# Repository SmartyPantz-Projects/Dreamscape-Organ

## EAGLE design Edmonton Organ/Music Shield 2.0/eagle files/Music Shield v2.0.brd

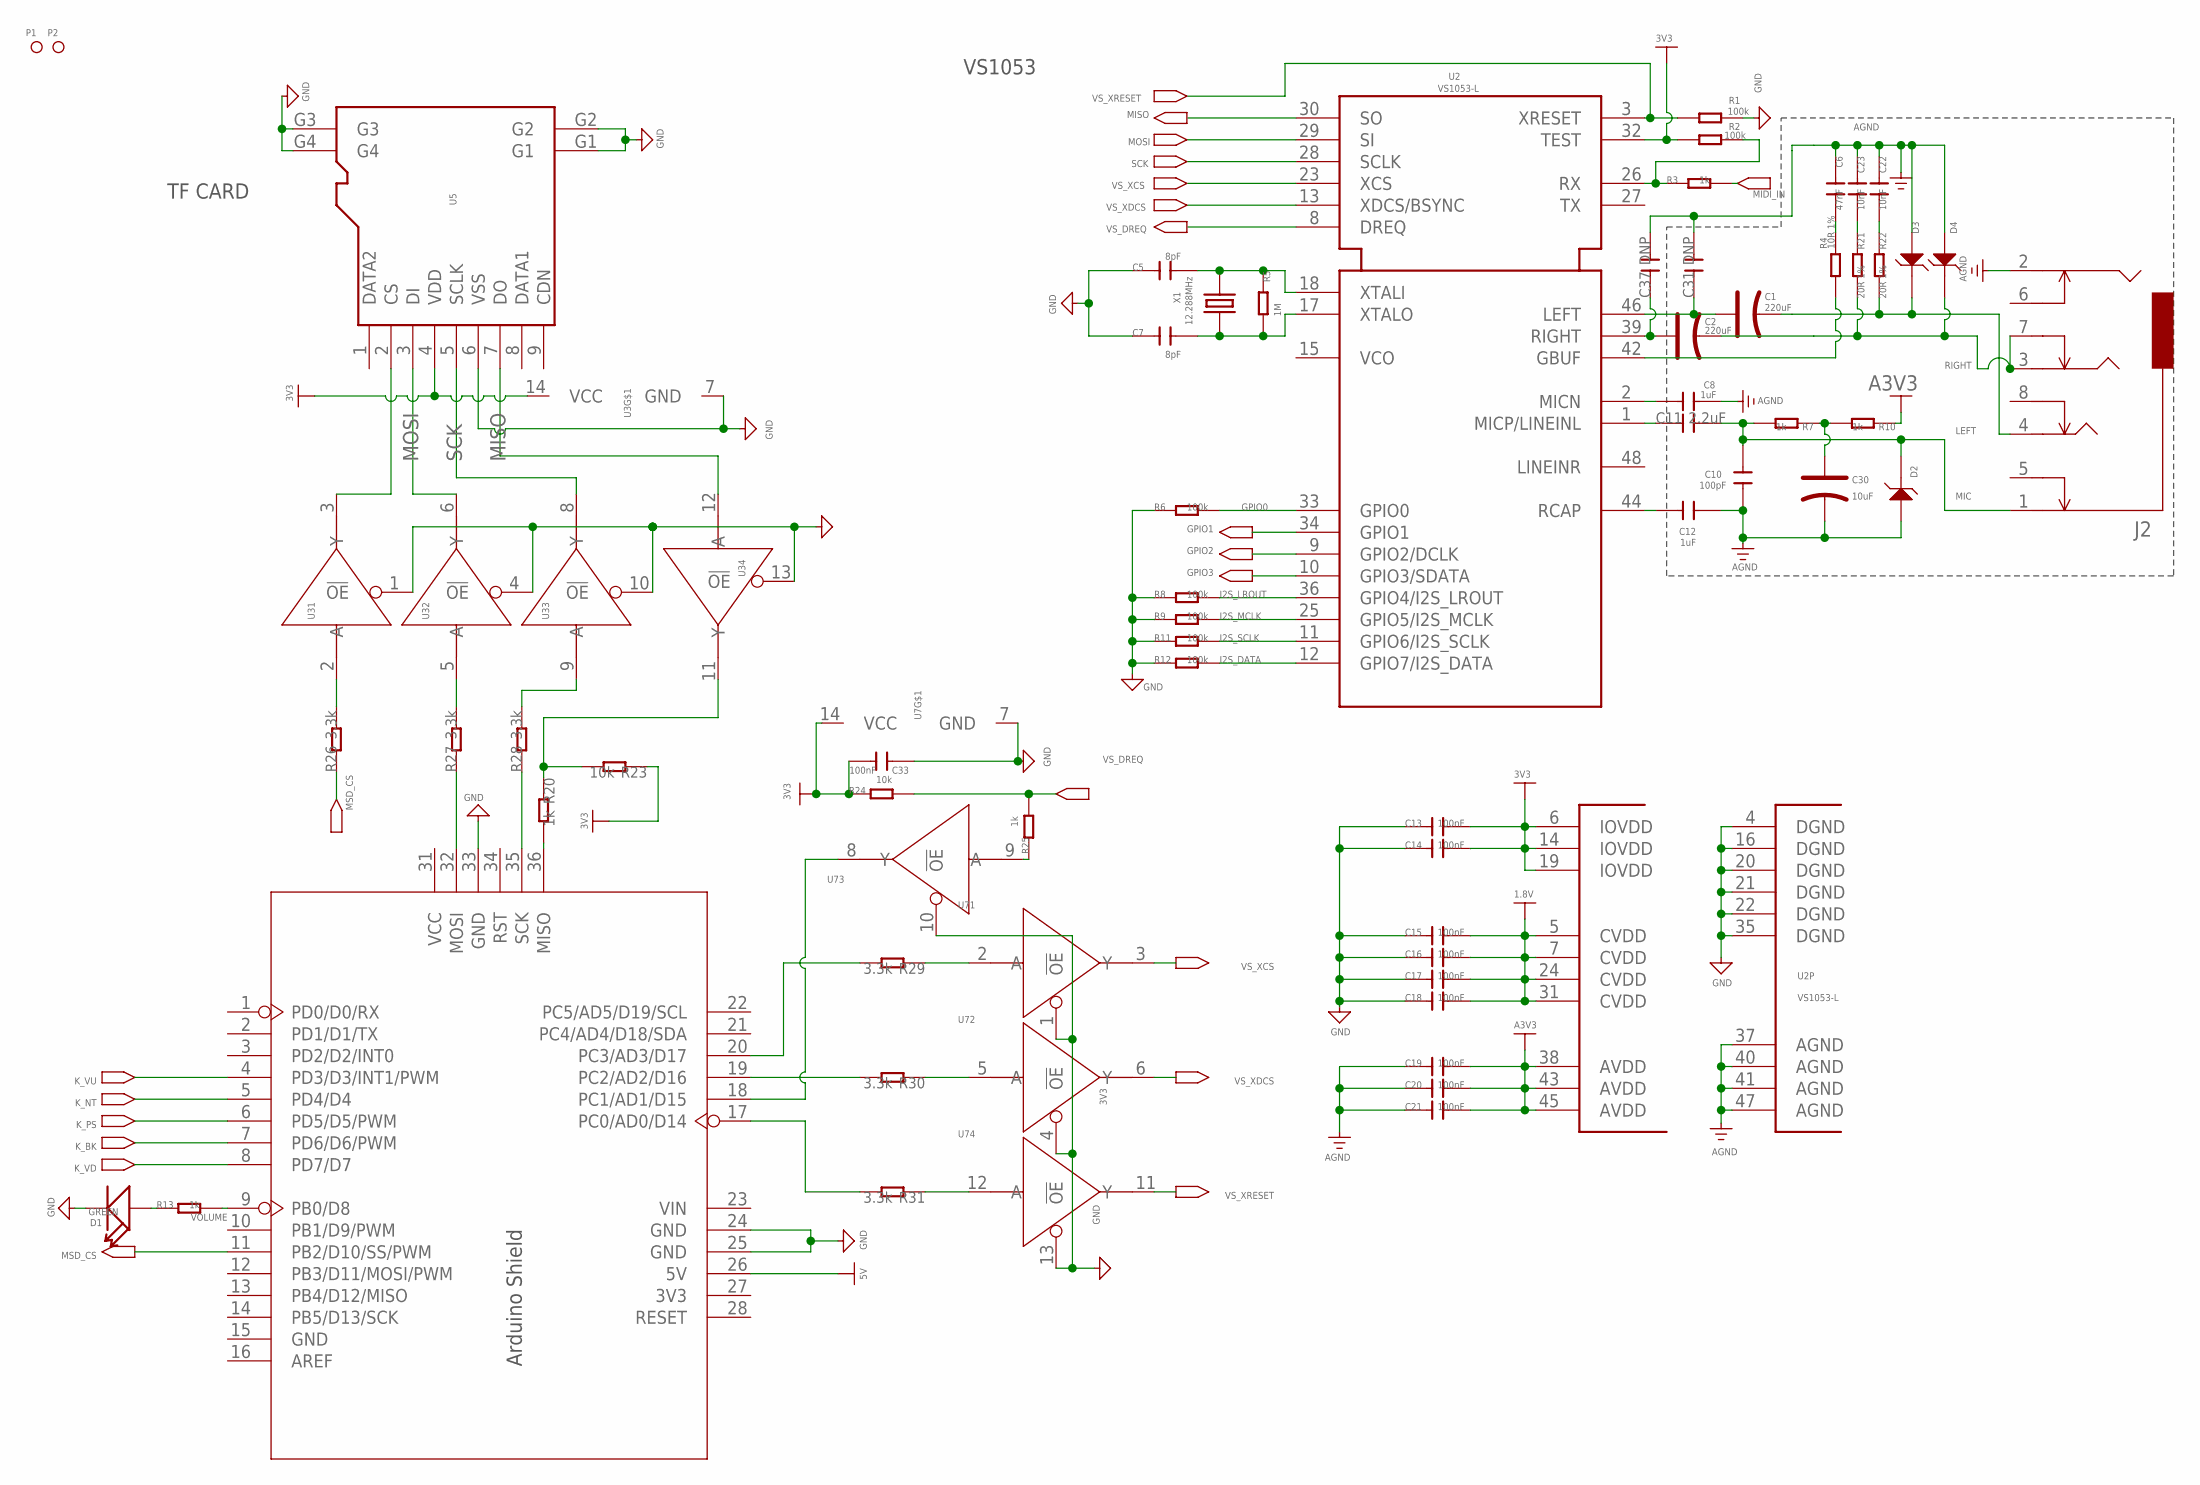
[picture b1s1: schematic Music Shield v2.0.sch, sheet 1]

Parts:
C1, C2: 220uF; AVX-B
C5, C7: 8pF; C0603
C6: 47nF; C0603
C8, C12: 1uF; C0603
C10: 100pF; C0603
C11: 2.2uF; C0805
C13, C14, C15, C16, C17, C18, C19, C20, C21, C33: 100nF; C0603
C22, C23: 10nF; C0603
C30: 10uF; AVX-A
C31, C37: DNP; C0603
D1: GREEN; LED-0603
D2, D3, D4: CESD5V0D1; SOD123-2.7X1.6
J2: AUDIO-8P'PJ-3536-L6S'; 8P-3.5-SMD
P1, P2: PAD-MARK; ROUND-MARK-1.0
R1, R2, R6, R8, R9, R11, R12: 100k; R0603
R3, R7, R10, R13, R20, R25: 1k; R0603
R4: 10R 1%; R0603
R5: 1M; R0603
R21, R22: 20R 1%; R0603
R23, R24: 10k; R0603
R26, R27, R28, R29, R30, R31: 3.3k; R0603
U2: VS1053-L; LQFP48
U3, U7: 74VHC125PW; TSSOP14
U5: HOLDER-MICROSD-9P; 9P-SMD-W/-RING
U9: ARDUINO
X1: 12.288MHz; 2P-SMD-5X3.2

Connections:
1.8V: C15.2, C16.2, C17.2, C18.2, U2.5 (CVDD), U2.7 (CVDD), U2.24 (CVDD), U2.31 (CVDD); also elsewhere on the board
3V3: C13.2, C14.2, C33.2, R2.1, R23.1, R24.1, U2.6 (IOVDD), U2.14 (IOVDD), U2.19 (IOVDD), U2.32 (TEST), U3.14 (VCC), U5.4 (VDD), U7.14 (VCC); also elsewhere on the board
5V: U9.26 (5V); also elsewhere on the board
A3V3: C19.2, C20.2, C21.2, R10.1, U2.38 (AVDD), U2.43 (AVDD), U2.45 (AVDD); also elsewhere on the board
AGND: C6.1, C8.2, C10.2, C12.1, C19.1, C20.1, C21.1, C22.1, C23.1, C30.-, C31.2, C37.2, D2.1, D3.1, D4.1, J2.2, U2.37 (AGND), U2.40 (AGND), U2.41 (AGND), U2.47 (AGND); also elsewhere on the board
GND: C5.1, C7.1, C13.1, C14.1, C15.1, C16.1, C17.1, C18.1, C33.1, D1.-, R1.2, R6.1, R8.1, R9.1, R11.1, R12.1, U2.4 (DGND), U2.16 (DGND), U2.20 (DGND), U2.21 (DGND), U2.22 (DGND), U2.35 (DGND), U3.1 (!OE), U3.4 (!OE), U3.7 (GND), U3.10 (!OE), U3.13 (!OE), U5.6 (VSS), U5.G1, U5.G2, U5.G3, U5.G4, U7.1 (!OE), U7.4 (!OE), U7.7 (GND), U7.10 (!OE), U7.13 (!OE), U9.24 (GND), U9.25 (GND), U9.33 (GND); also elsewhere on the board
GPIO0: R6.2, U2.33 (GPIO0)
GPIO1: U2.34 (GPIO1); also elsewhere on the board
GPIO2: U2.9 (GPIO2/DCLK); also elsewhere on the board
GPIO3: U2.10 (GPIO3/SDATA); also elsewhere on the board
I2S_DATA: R12.2, U2.12 (GPIO7/I2S_DATA); also elsewhere on the board
I2S_LROUT: R8.2, U2.36 (GPIO4/I2S_LROUT); also elsewhere on the board
I2S_MCLK: R9.2, U2.25 (GPIO5/I2S_MCLK); also elsewhere on the board
I2S_SCLK: R11.2, U2.11 (GPIO6/I2S_SCLK); also elsewhere on the board
K_BK: U9.7 (PD6/D6/PWM); also elsewhere on the board
K_NT: U9.5 (PD4/D4); also elsewhere on the board
K_PS: U9.6 (PD5/D5/PWM); also elsewhere on the board
K_VD: U9.8 (PD7/D7); also elsewhere on the board
K_VU: U9.4 (PD3/D3/INT1/PWM); also elsewhere on the board
LEFT: C1.-, D3.2, J2.4, R22.2
MIC: C10.1, C11.2, D2.2, J2.1, R7.2
MIDI_IN: R3.2; also elsewhere on the board
MISO: U2.30 (SO), U3.12 (A), U5.7 (DO)
MOSI: U2.29 (SI), U3.6 (Y), U5.3 (DI)
MSD_CS: R26.1, U9.11 (PB2/D10/SS/PWM)
unnamed: C5.2, R5.1, U2.18 (XTALI), X1.2
unnamed: C7.2, R5.2, U2.17 (XTALO), X1.1
unnamed: C12.2, U2.44 (RCAP)
unnamed: C30.+, R7.1, R10.2
unnamed: C22.2, R22.1
unnamed: C2.+, C37.1, U2.39 (RIGHT)
unnamed: C8.1, U2.2 (MICN)
unnamed: C1.+, C31.1, U2.46 (LEFT)
unnamed: C6.2, R4.2
unnamed: C23.2, R21.1
unnamed: C11.1, U2.1 (MICP/LINEINL)
unnamed: R2.2, R3.1, U2.26 (RX)
unnamed: R31.2, U9.17 (PC0/AD0/D14)
unnamed: R4.1, U2.42 (GBUF)
unnamed: R26.2, U3.2 (A)
unnamed: R29.1, U7.2 (A)
unnamed: R27.2, U3.5 (A)
unnamed: R30.1, U7.5 (A)
unnamed: R31.1, U7.12 (A)
unnamed: U3.3 (Y), U5.2 (CS)
unnamed: R29.2, U9.20 (PC3/AD3/D17)
unnamed: R30.2, U9.19 (PC2/AD2/D16)
unnamed: U7.8 (Y), U9.18 (PC1/AD1/D15)
unnamed: R27.1, U9.32 (MOSI)
unnamed: R28.1, U9.35 (SCK)
unnamed: R20.2, U9.36 (MISO)
unnamed: D1.+, R13.1
unnamed: R25.1, U7.9 (A)
unnamed: R20.1, R23.2, U3.11 (Y)
unnamed: R28.2, U3.9 (A)
RIGHT: C2.-, D4.2, J2.3, J2.7, R21.2
SCK: U2.28 (SCLK), U3.8 (Y), U5.5 (SCLK)
VOLUME: R13.2, U9.9 (PB0/D8)
VS_DREQ: R24.2, R25.2, U2.8 (DREQ)
VS_XCS: U2.23 (XCS), U7.3 (Y)
VS_XDCS: U2.13 (XDCS/BSYNC), U7.6 (Y)
VS_XRESET: R1.1, U2.3 (XRESET), U7.11 (Y)

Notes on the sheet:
Arduino Shield
TF CARD
VS1053

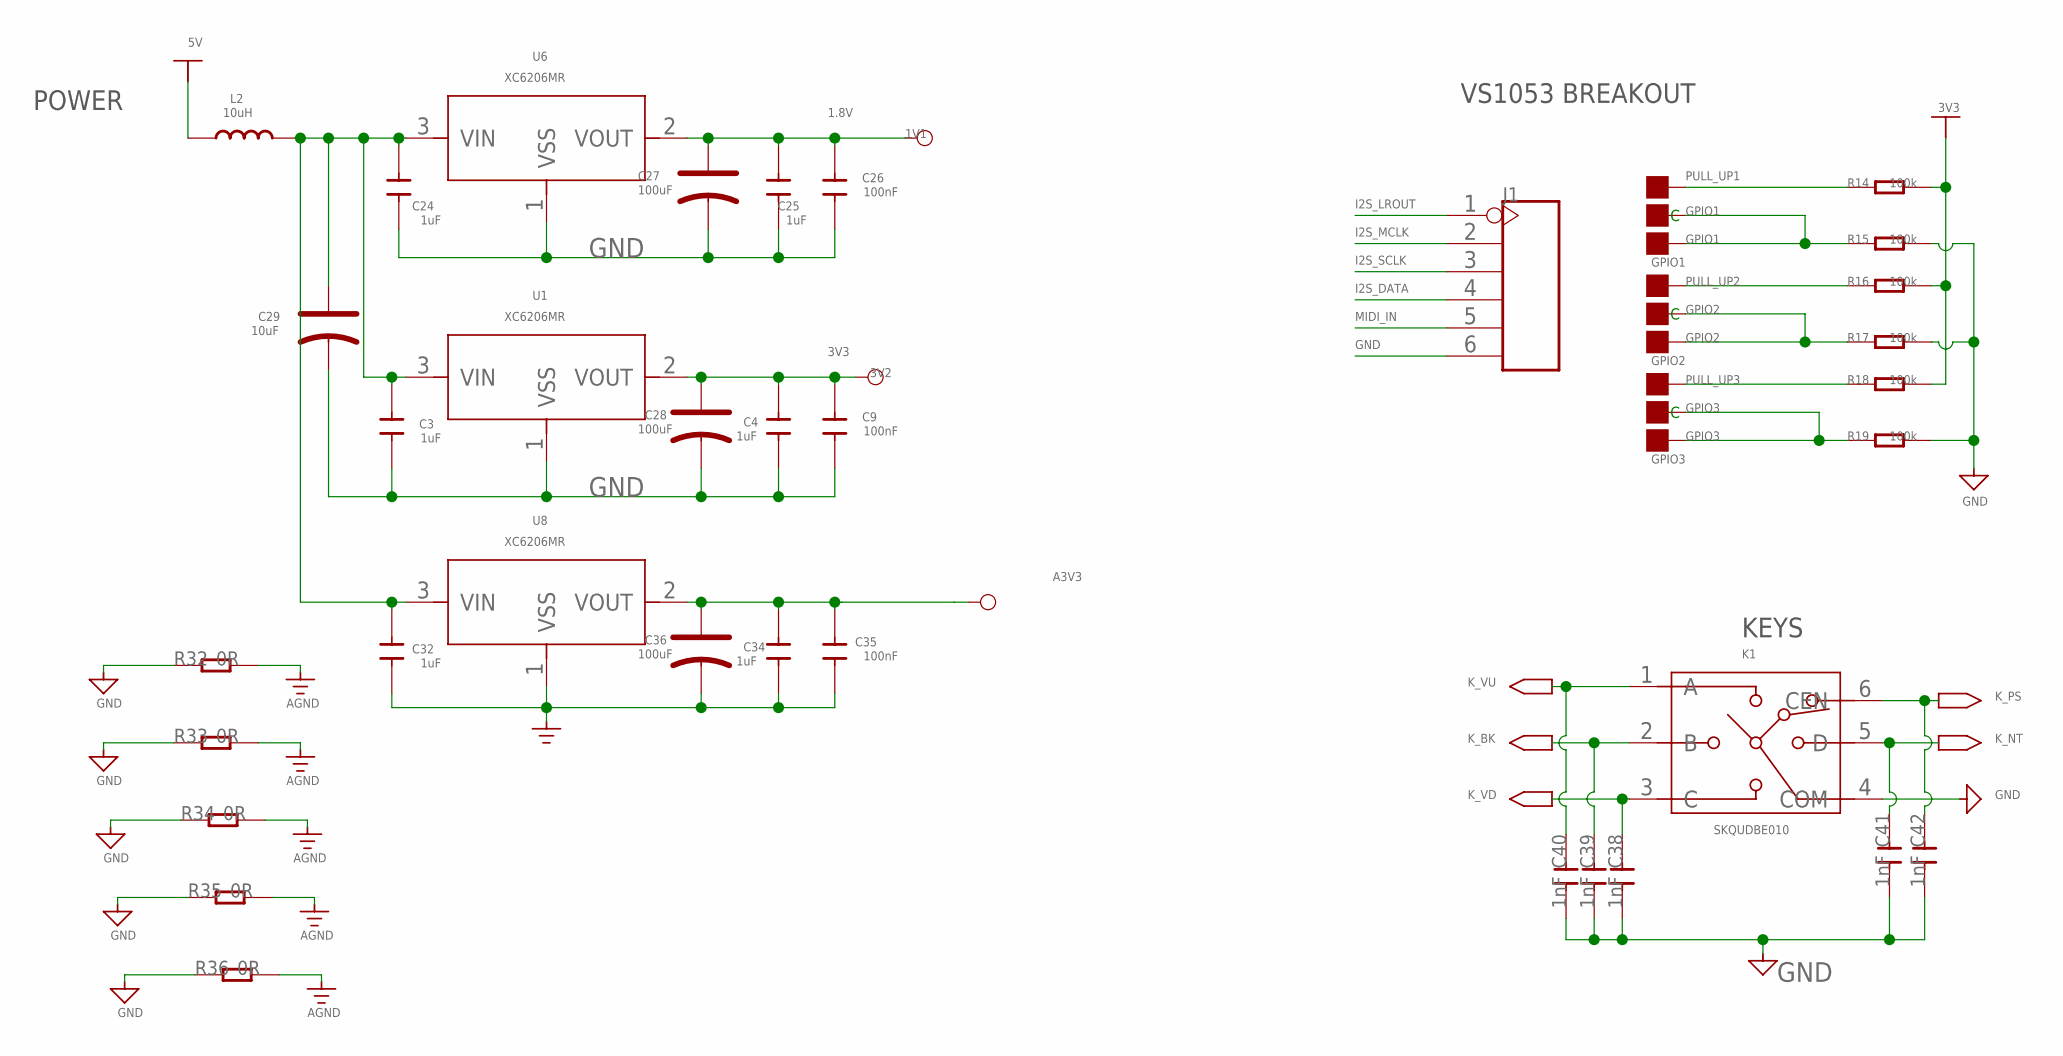
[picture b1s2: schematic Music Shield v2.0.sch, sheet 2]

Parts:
1V1, 3V2: TEST_POINT_SIZE_3030; TP_3535
A3V3: TEST_POINT_SIZE_3030; TP_3535
C3, C4, C24, C25, C32, C34: 1uF; C0603
C9, C26, C35: 100nF; C0603
C27, C28, C36: 100uF; AVX-B
C29: 10uF; AVX-A
C38, C39, C40, C41, C42: 1nF; C0603
GPIO1, GPIO2, GPIO3: PAD-JUMPER-3P-40*40; 3P-SMD-4.1X1.5
J1: HEADER-6P-55/35MIL; 6P-2.54-55/35MIL
K1: SKQUDBE010; 6P-10X10X8.6MM
L2: 10uH; 0806
R14, R15, R16, R17, R18, R19: 100k; R0603
R32, R33, R34, R35, R36: 0R; R0603
U1, U6, U8: XC6206MR; SOT23

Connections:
1.8V: 1V1.T, C25.2, C26.2, C27.+, U6.2 (VOUT); also elsewhere on the board
3V3: 3V2.T, C4.2, C9.2, C28.+, R14.2, R16.2, R18.2, U1.2 (VOUT); also elsewhere on the board
5V: L2.1; also elsewhere on the board
A3V3: A3V3.T, C34.2, C35.2, C36.+, U8.2 (VOUT); also elsewhere on the board
AGND: C32.1, C34.1, C35.1, C36.-, R32.2, R33.2, R34.2, R35.2, R36.2, U8.1 (VSS); also elsewhere on the board
GND: C3.1, C4.1, C9.1, C24.1, C25.1, C26.1, C27.-, C28.-, C29.-, C38.2, C39.2, C40.2, C41.2, C42.2, J1.6, K1.4 (COM), R15.2, R17.2, R19.2, R32.1, R33.1, R34.1, R35.1, R36.1, U1.1 (VSS), U6.1 (VSS); also elsewhere on the board
GPIO1: GPIO1.00 (L), GPIO1.MM (C), R15.1; also elsewhere on the board
GPIO2: GPIO2.00 (L), GPIO2.MM (C), R17.1; also elsewhere on the board
GPIO3: GPIO3.00 (L), GPIO3.MM (C), R19.1; also elsewhere on the board
I2S_DATA: J1.4; also elsewhere on the board
I2S_LROUT: J1.1; also elsewhere on the board
I2S_MCLK: J1.2; also elsewhere on the board
I2S_SCLK: J1.3; also elsewhere on the board
K_BK: C39.1, K1.2 (B); also elsewhere on the board
K_NT: C41.1, K1.5 (D); also elsewhere on the board
K_PS: C42.1, K1.6 (CEN); also elsewhere on the board
K_VD: C38.1, K1.3 (C); also elsewhere on the board
K_VU: C40.1, K1.1 (A); also elsewhere on the board
MIDI_IN: J1.5; also elsewhere on the board
unnamed: C3.2, C24.2, C29.+, C32.2, L2.2, U1.3 (VIN), U6.3 (VIN), U8.3 (VIN)
PULL_UP1: GPIO1.11 (R), R14.1
PULL_UP2: GPIO2.11 (R), R16.1
PULL_UP3: GPIO3.11 (R), R18.1

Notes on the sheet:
POWER
VS1053 BREAKOUT
KEYS

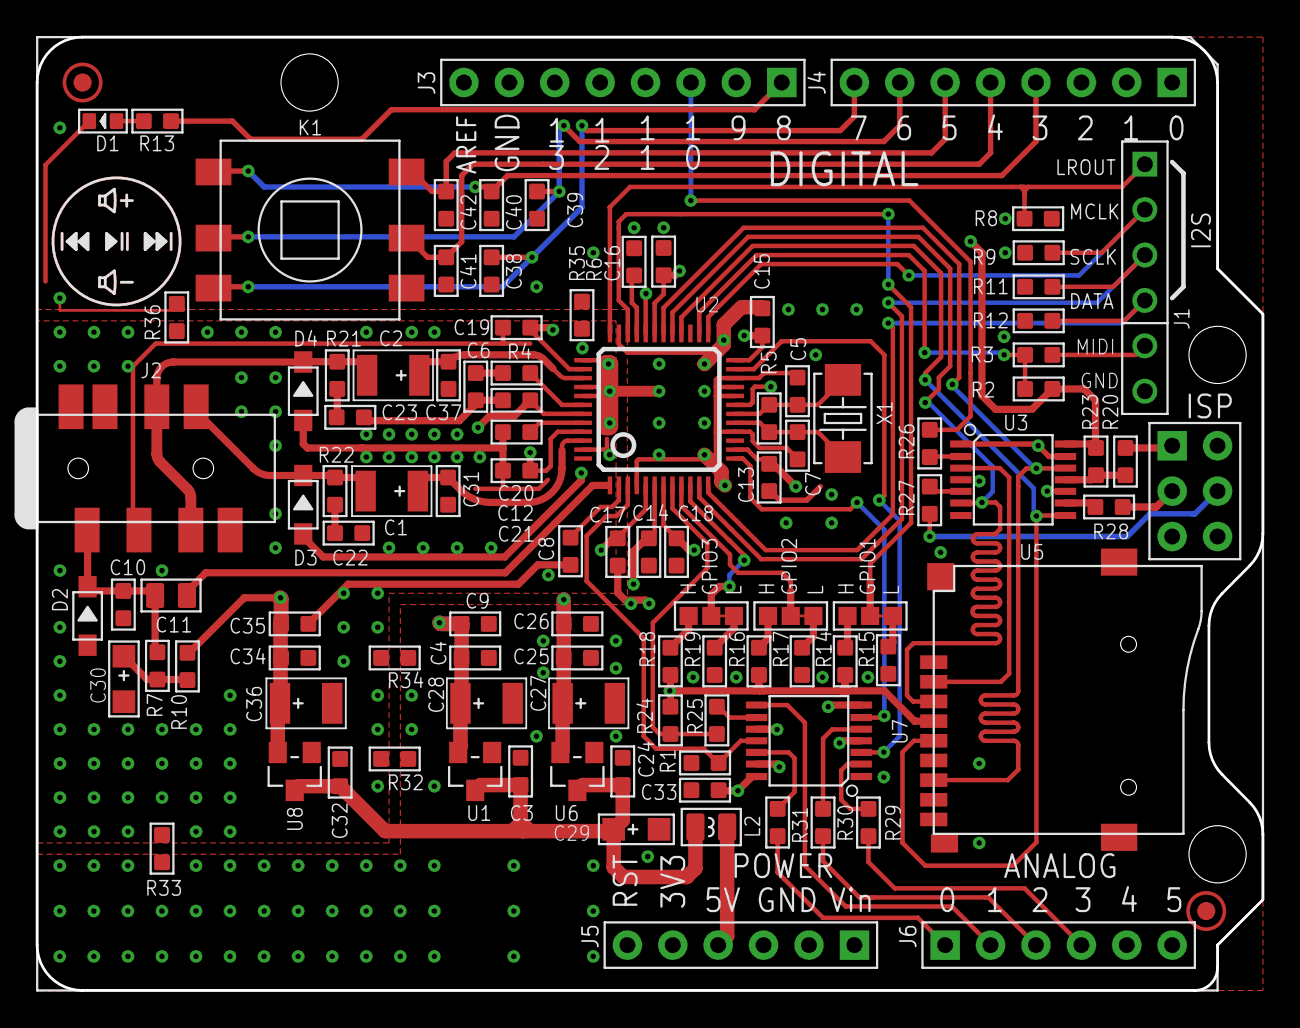
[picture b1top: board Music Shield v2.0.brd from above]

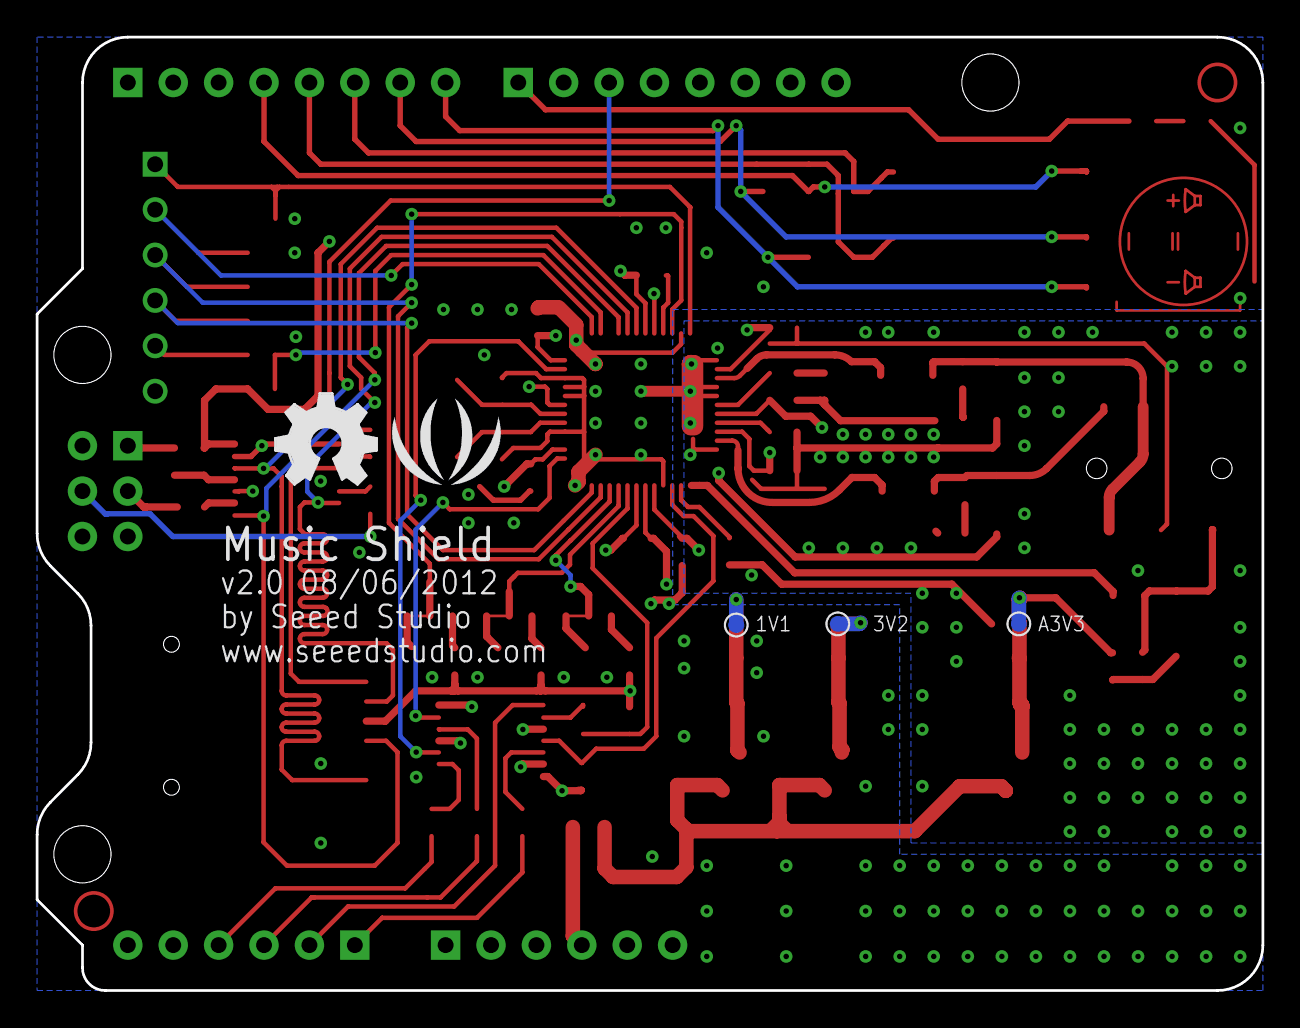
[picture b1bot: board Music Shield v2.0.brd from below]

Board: 4 copper layers, 68.6 x 53.3 mm, 105 parts (5 on the bottom side), 66 nets.

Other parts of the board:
U$1: LOGO_SILK
U$2: OSHW_FILLX200_NOTEXT

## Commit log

2016-06-17 reshuffle
